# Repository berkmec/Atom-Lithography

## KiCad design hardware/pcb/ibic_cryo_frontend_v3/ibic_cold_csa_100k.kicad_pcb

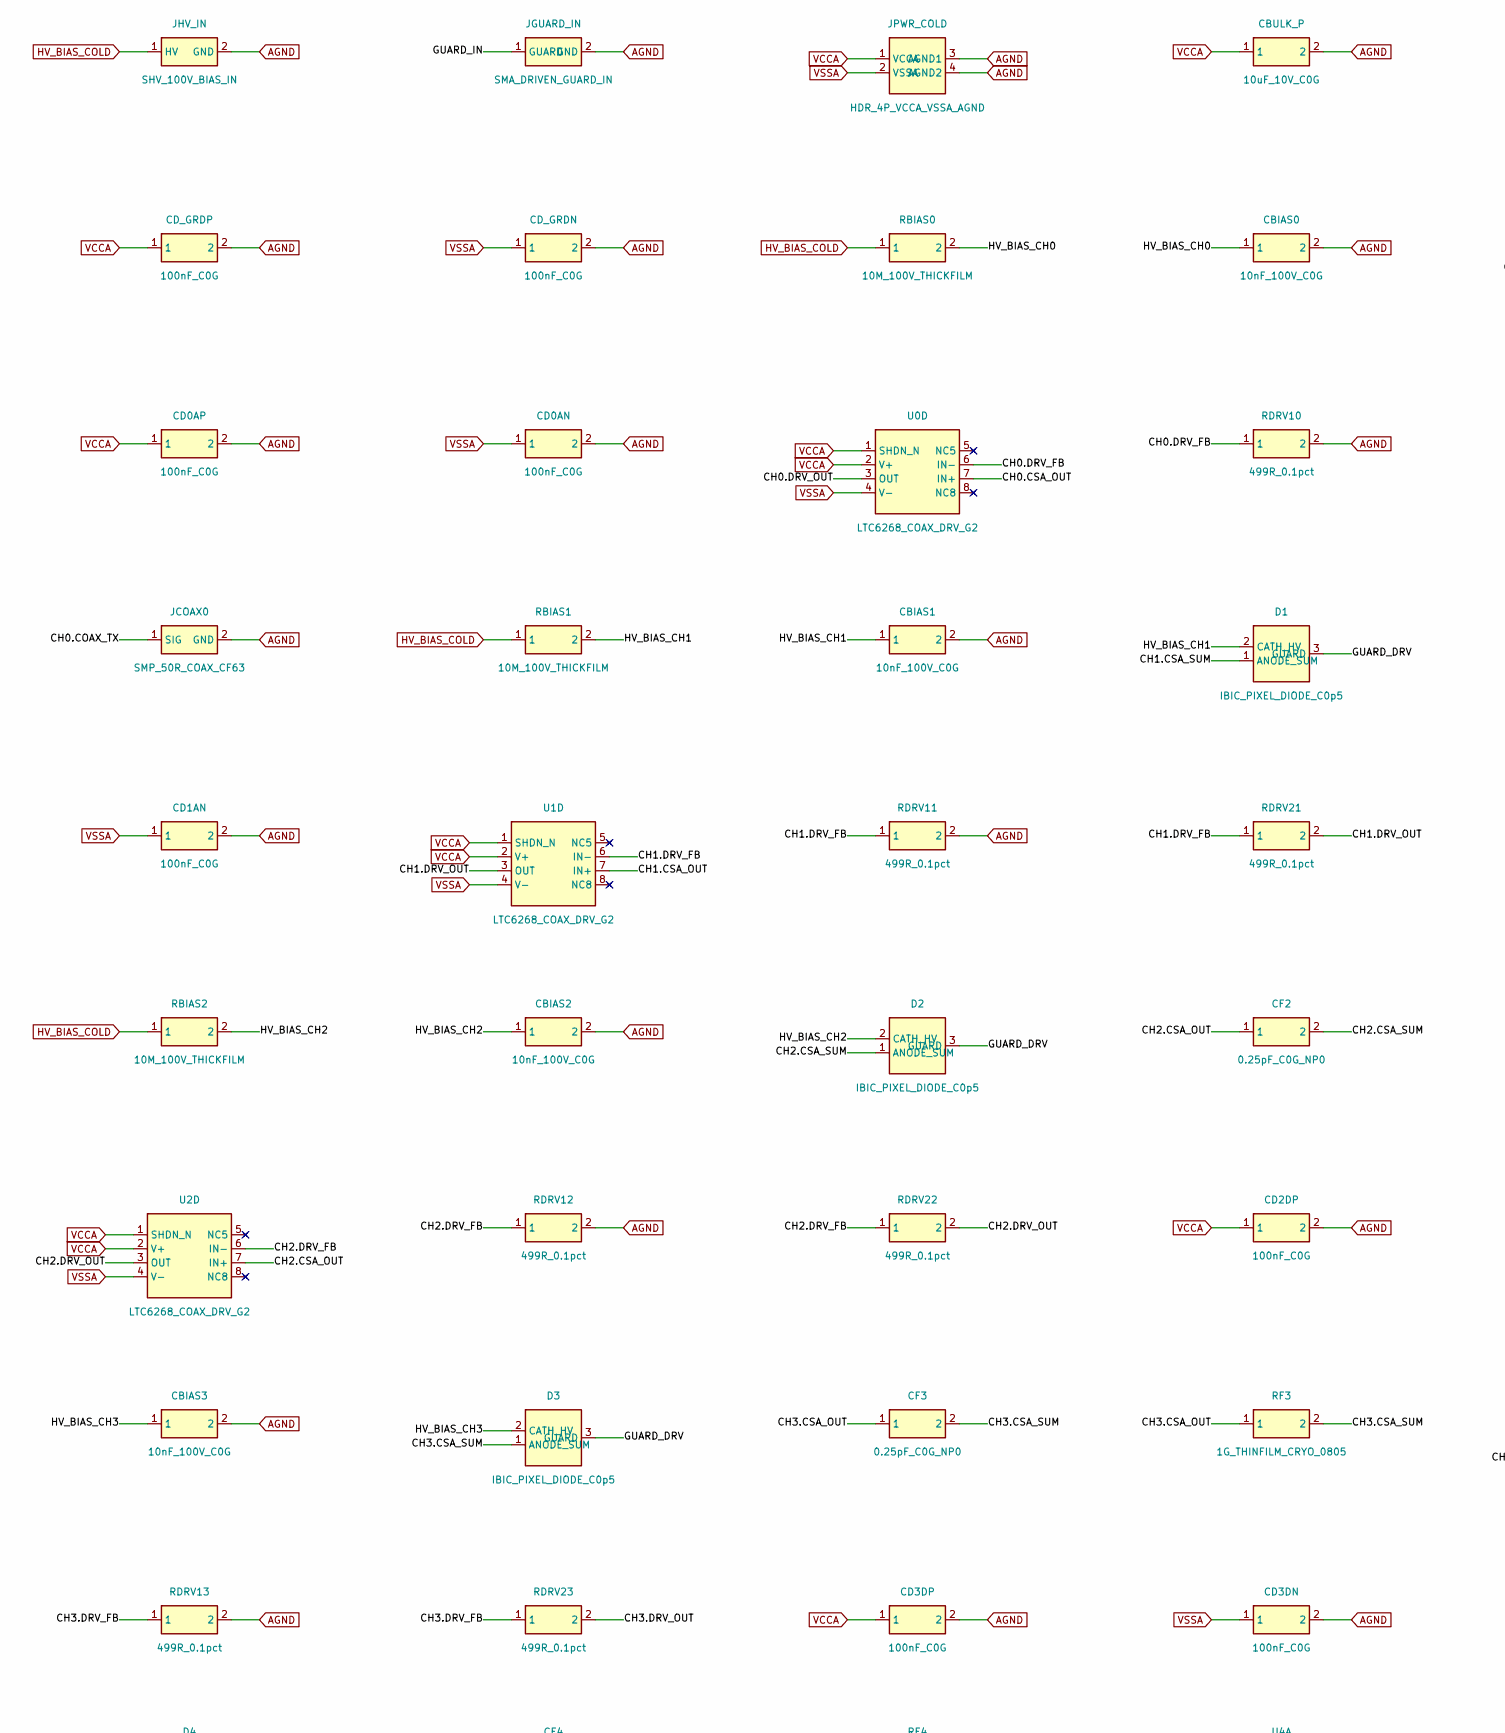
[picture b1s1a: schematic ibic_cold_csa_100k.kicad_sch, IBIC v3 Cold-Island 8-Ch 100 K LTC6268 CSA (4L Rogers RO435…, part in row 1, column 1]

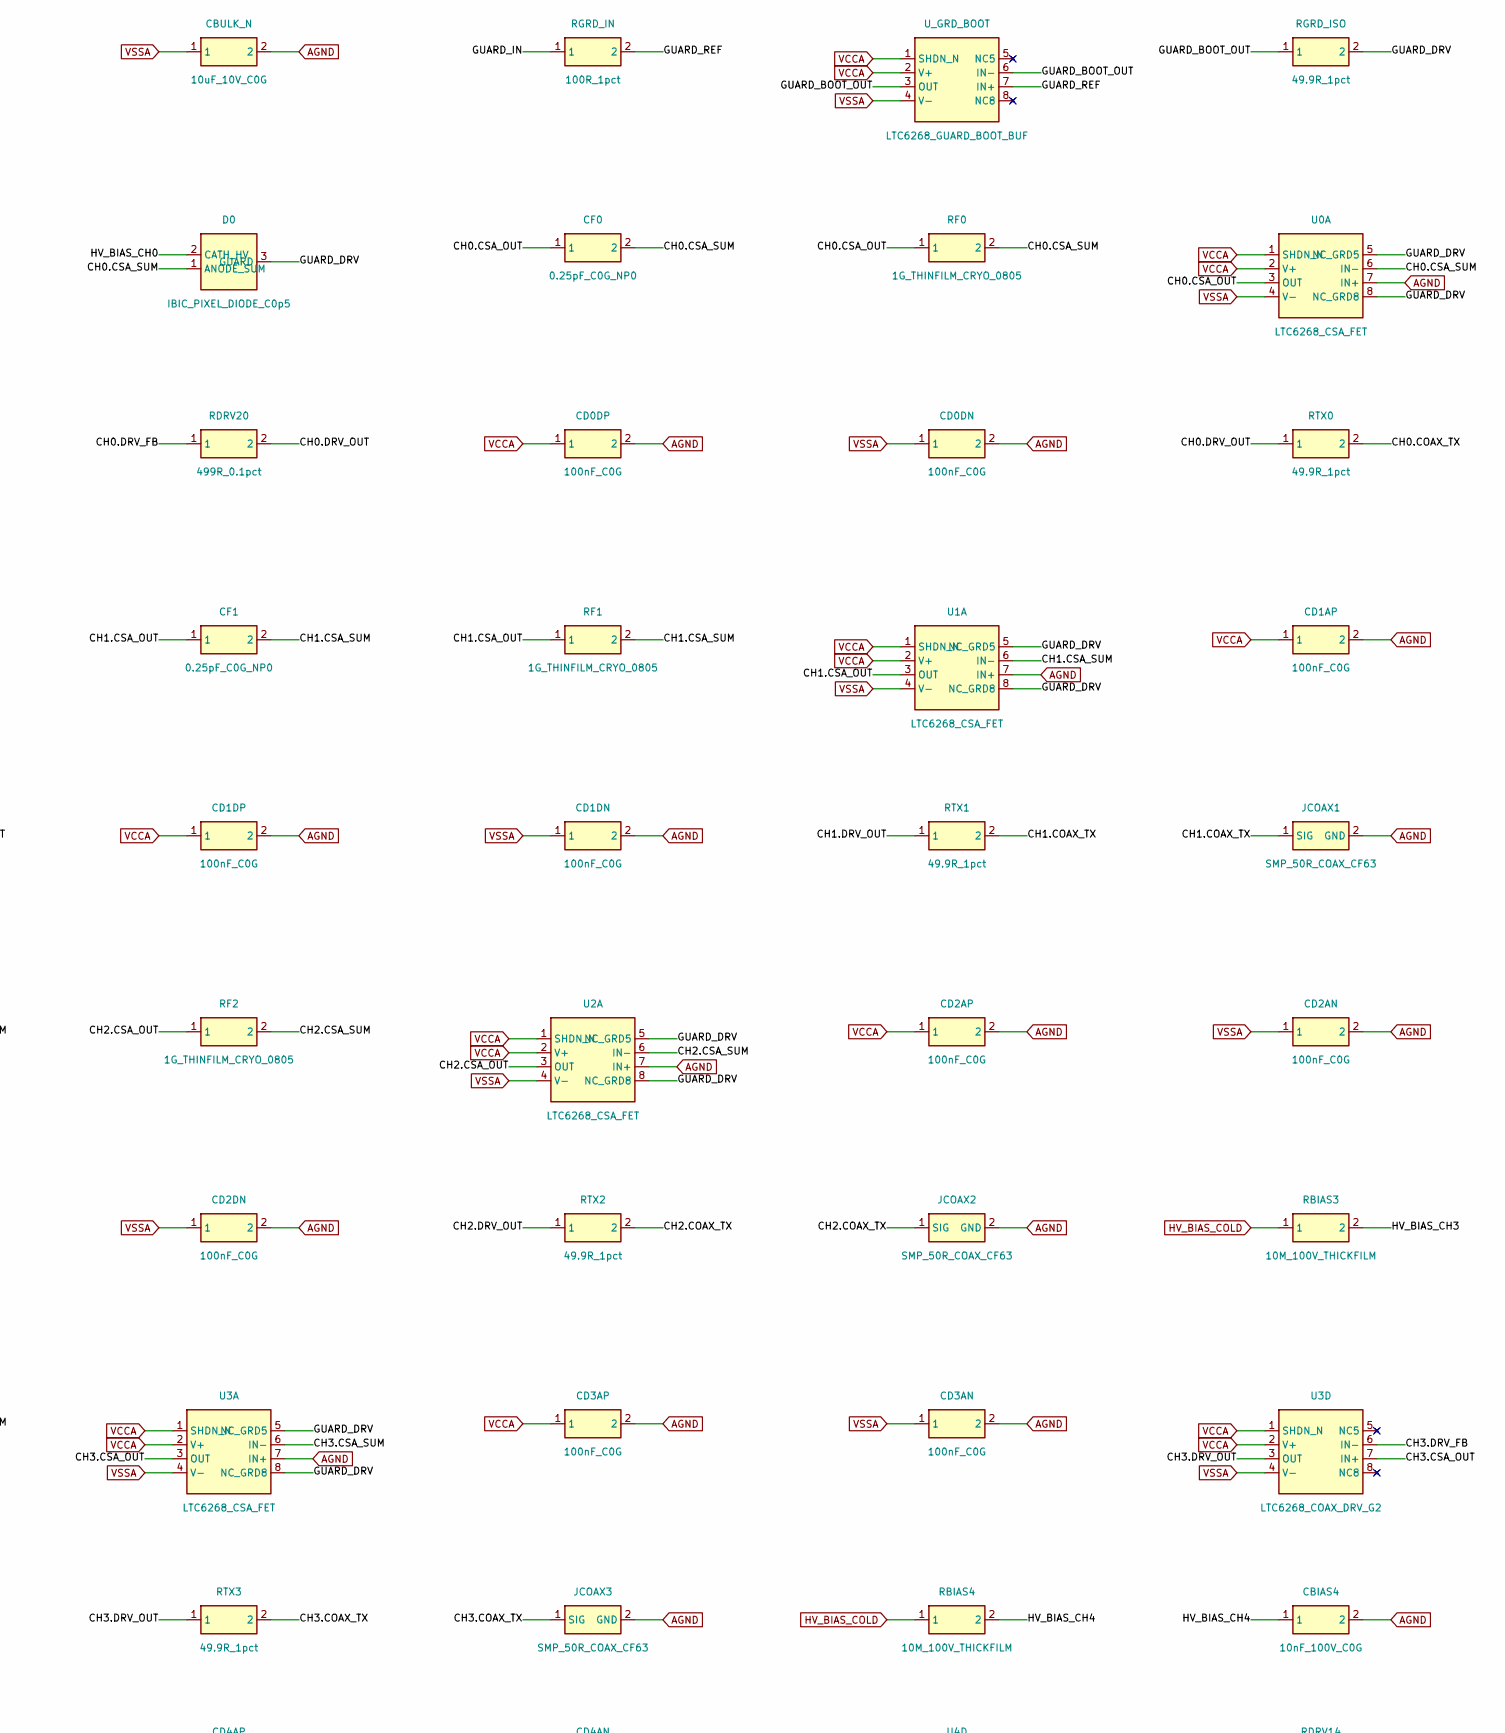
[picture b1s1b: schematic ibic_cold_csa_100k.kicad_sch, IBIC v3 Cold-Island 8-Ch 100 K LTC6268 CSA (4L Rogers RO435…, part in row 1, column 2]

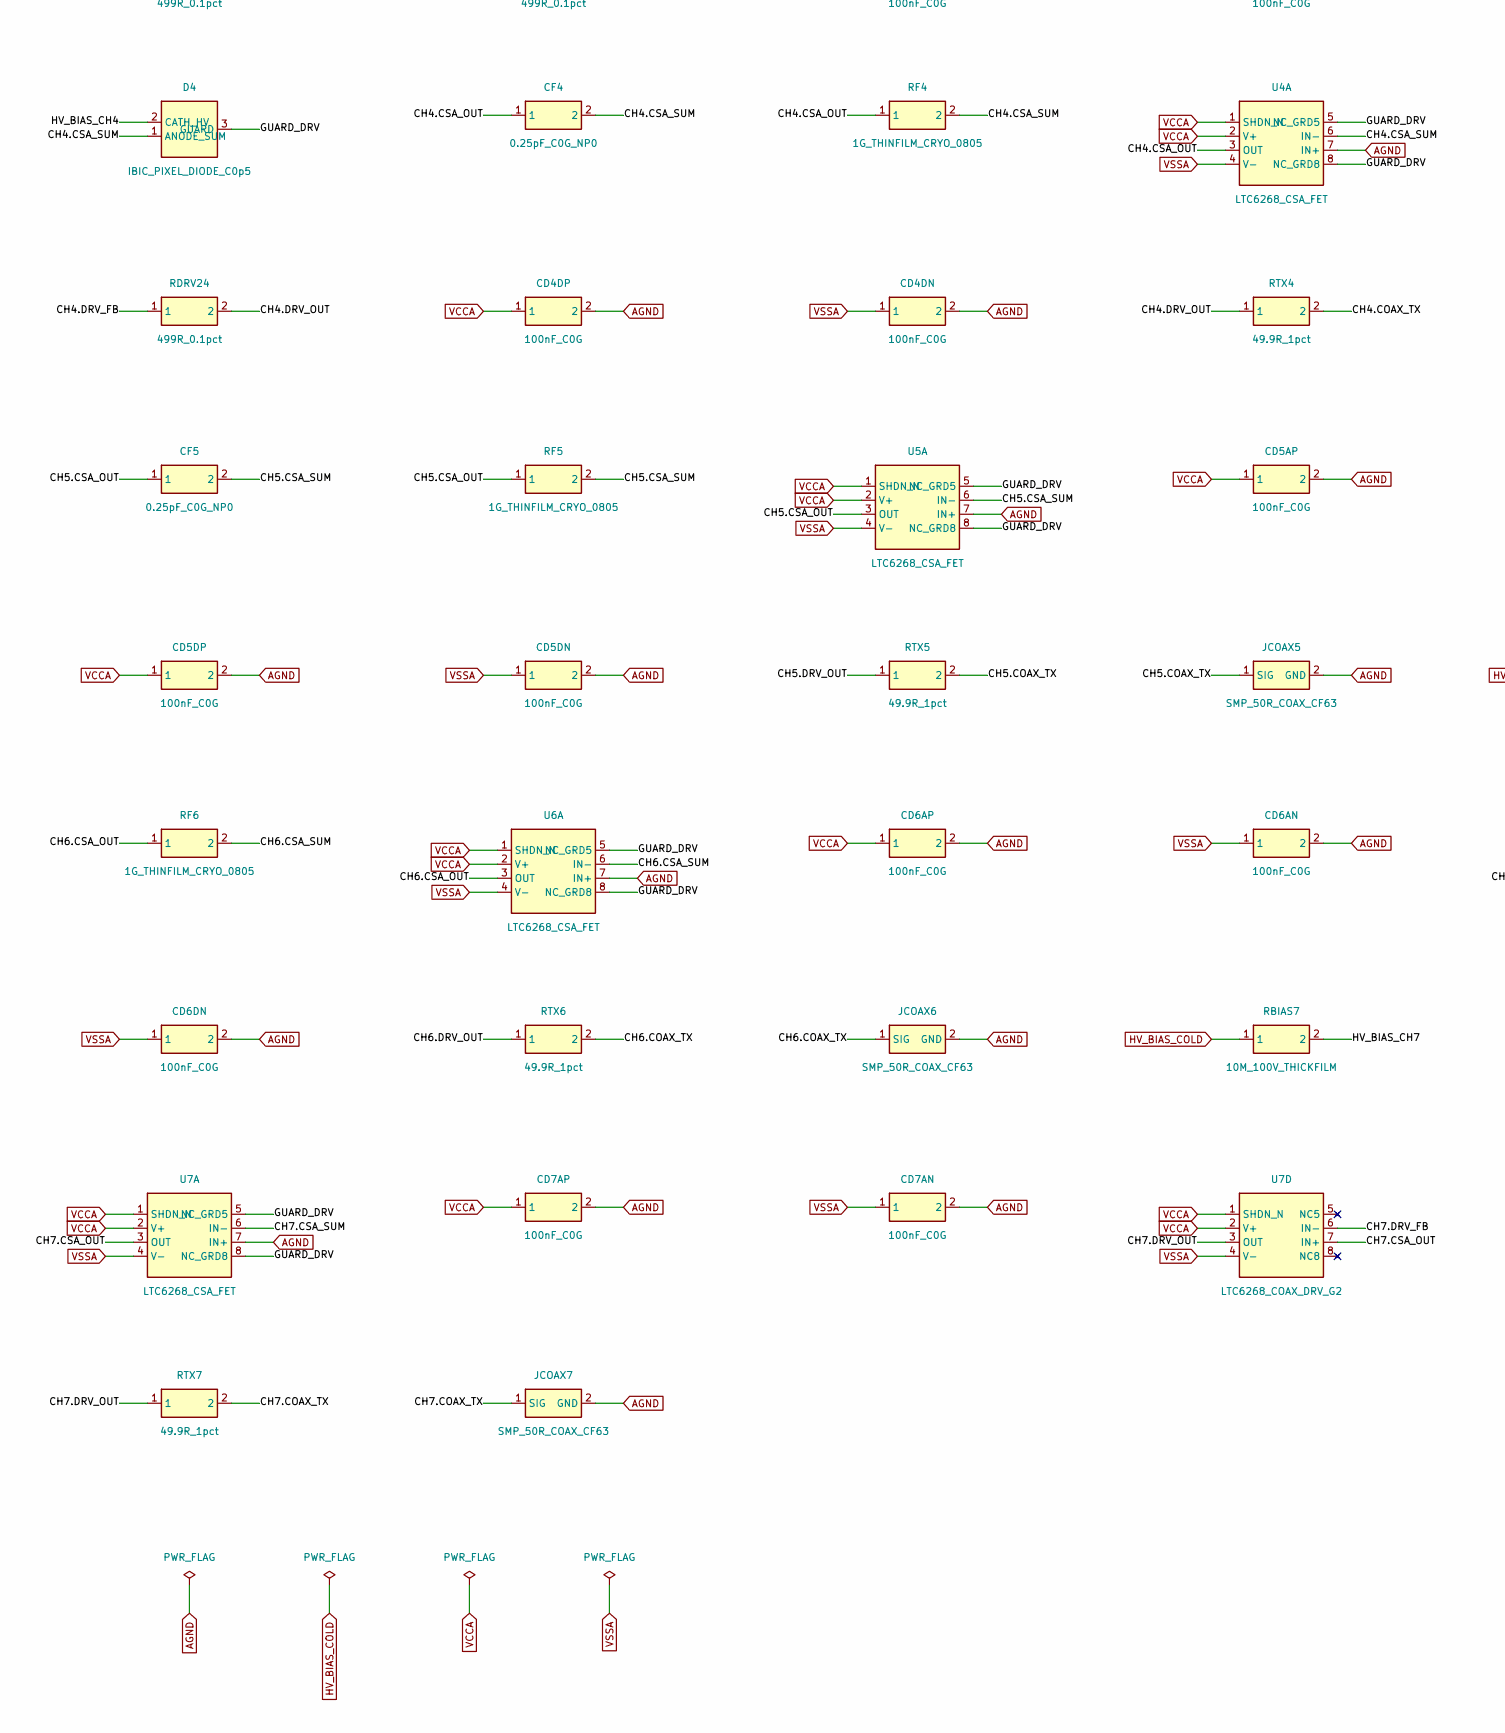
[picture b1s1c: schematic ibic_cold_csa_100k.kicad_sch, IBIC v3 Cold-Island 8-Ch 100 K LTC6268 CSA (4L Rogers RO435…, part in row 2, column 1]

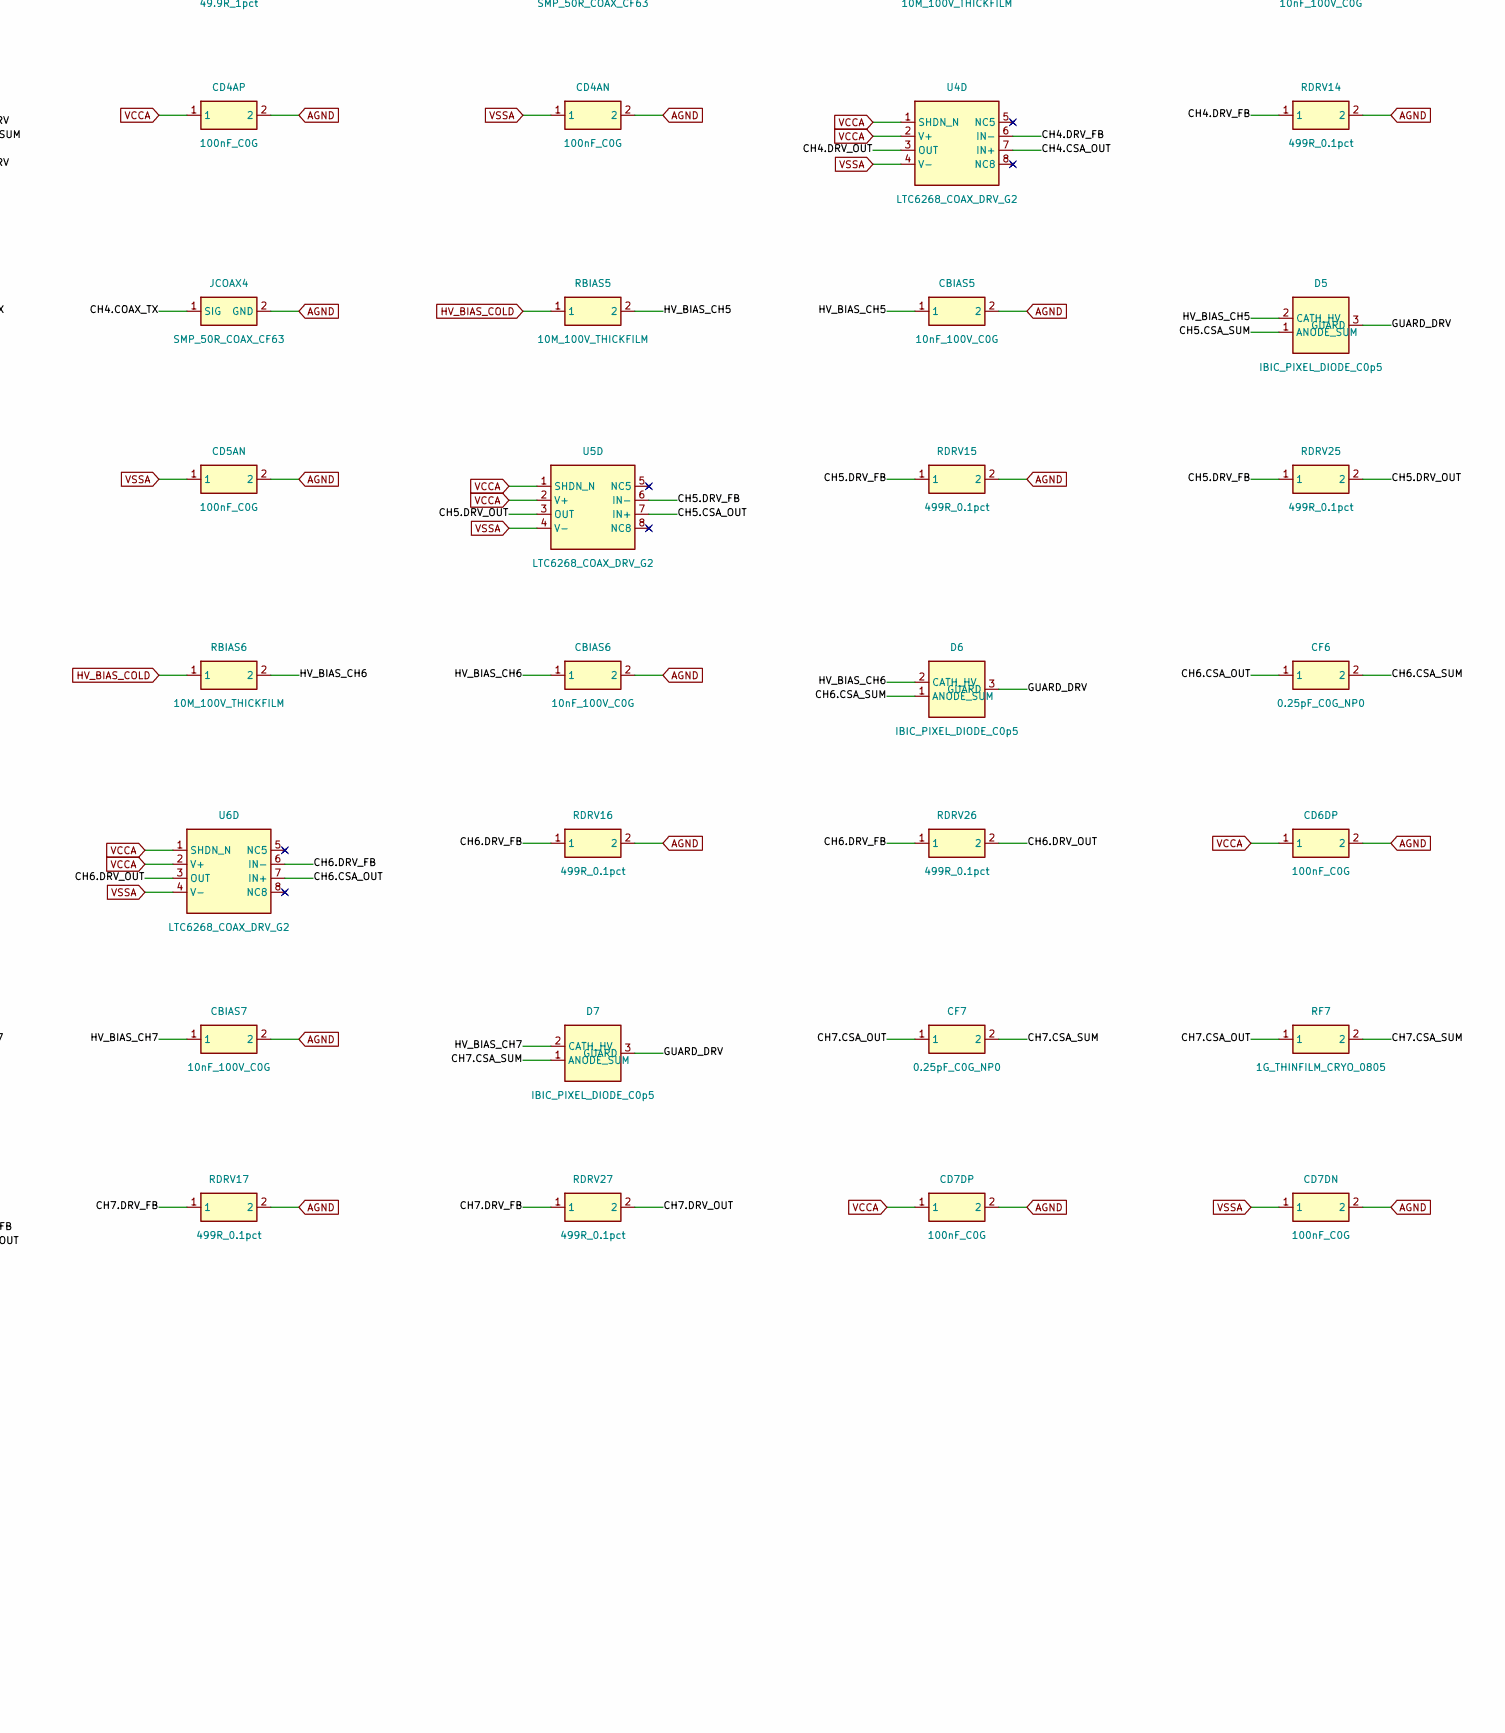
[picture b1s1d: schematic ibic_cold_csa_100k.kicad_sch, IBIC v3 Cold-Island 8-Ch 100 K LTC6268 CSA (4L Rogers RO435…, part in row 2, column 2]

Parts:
CBIAS0, CBIAS1, CBIAS2, CBIAS3, CBIAS4, CBIAS5, CBIAS6, CBIAS7: 10nF_100V_C0G; C_1206_3216Metric; MPN 10nF_100V_C0G
CBULK_N: 10uF_10V_C0G; C_0805_2012Metric; MPN 10uF_10V_C0G
CBULK_P: 10uF_10V_C0G; C_0805_2012Metric; MPN 10uF_10V_C0G
CD0AN, CD0AP, CD0DN, CD0DP, CD1AN, CD1AP, CD1DN, CD1DP, CD2AN, CD2AP, CD2DN, CD2DP, CD3AN, CD3AP, CD3DN, CD3DP, CD4AN, CD4AP, CD4DN, CD4DP, CD5AN, CD5AP, CD5DN, CD5DP, CD6AN, CD6AP, CD6DN, CD6DP, CD7AN, CD7AP, CD7DN, CD7DP: 100nF_C0G; C_0402_1005Metric; MPN 100nF_C0G
CD_GRDN: 100nF_C0G; C_0402_1005Metric; MPN 100nF_C0G
CD_GRDP: 100nF_C0G; C_0402_1005Metric; MPN 100nF_C0G
CF0, CF1, CF2, CF3, CF4, CF5, CF6, CF7: 0.25pF_C0G_NP0; C_0402_1005Metric; MPN 0.25pF_C0G_NP0
D0, D1, D2, D3, D4, D5, D6, D7: IBIC_PIXEL_DIODE_C0p5; IBIC_PIXEL_FLIPCHIP_3P; MPN IBIC_PIXEL_DIODE_C0p5
JCOAX0, JCOAX1, JCOAX2, JCOAX3, JCOAX4, JCOAX5, JCOAX6, JCOAX7: SMP_50R_COAX_CF63; SMA_EdgeMount; MPN SMP_50R_COAX_CF63
JGUARD_IN: SMA_DRIVEN_GUARD_IN; SMA_EdgeMount; MPN SMA_DRIVEN_GUARD_IN
JHV_IN: SHV_100V_BIAS_IN; SHV_Amphenol_HV; MPN SHV_100V_BIAS_IN
JPWR_COLD: HDR_4P_VCCA_VSSA_AGND; HDR_1x4_2.54mm; MPN HDR_4P_VCCA_VSSA_AGND
RBIAS0, RBIAS1, RBIAS2, RBIAS3, RBIAS4, RBIAS5, RBIAS6, RBIAS7: 10M_100V_THICKFILM; R_1206_3216Metric; MPN 10M_100V_THICKFILM
RDRV10, RDRV11, RDRV12, RDRV13, RDRV14, RDRV15, RDRV16, RDRV17, RDRV20, RDRV21, RDRV22, RDRV23, RDRV24, RDRV25, RDRV26, RDRV27: 499R_0.1pct; R_0402_1005Metric; MPN 499R_0.1pct
RF0, RF1, RF2, RF3, RF4, RF5, RF6, RF7: 1G_THINFILM_CRYO_0805; R_0805_2012Metric; MPN CHV0805-1G0-THINFILM-CRYO
RGRD_IN: 100R_1pct; R_0603_1608Metric; MPN 100R_1pct
RGRD_ISO: 49.9R_1pct; R_0603_1608Metric; MPN 49.9R_1pct
RTX0, RTX1, RTX2, RTX3, RTX4, RTX5, RTX6, RTX7: 49.9R_1pct; R_0402_1005Metric; MPN 49.9R_1pct
U0A, U1A, U2A, U3A, U4A, U5A, U6A, U7A: LTC6268_CSA_FET; SOIC-8_3.9x4.9mm_P1.27mm; MPN LTC6268IS8
U0D, U1D, U2D, U3D, U4D, U5D, U6D, U7D: LTC6268_COAX_DRV_G2; SOIC-8_3.9x4.9mm_P1.27mm; MPN LTC6268IS8
U_GRD_BOOT: LTC6268_GUARD_BOOT_BUF; SOIC-8_3.9x4.9mm_P1.27mm; MPN LTC6268IS8

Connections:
AGND: CBIAS0.2, CBIAS1.2, CBIAS2.2, CBIAS3.2, CBIAS4.2, CBIAS5.2, CBIAS6.2, CBIAS7.2, CBULK_N.2, CBULK_P.2, CD0AN.2, CD0AP.2, CD0DN.2, CD0DP.2, CD1AN.2, CD1AP.2, CD1DN.2, CD1DP.2, CD2AN.2, CD2AP.2, CD2DN.2, CD2DP.2, CD3AN.2, CD3AP.2, CD3DN.2, CD3DP.2, CD4AN.2, CD4AP.2, CD4DN.2, CD4DP.2, CD5AN.2, CD5AP.2, CD5DN.2, CD5DP.2, CD6AN.2, CD6AP.2, CD6DN.2, CD6DP.2, CD7AN.2, CD7AP.2, CD7DN.2, CD7DP.2, CD_GRDN.2, CD_GRDP.2, JCOAX0.2 (GND), JCOAX1.2 (GND), JCOAX2.2 (GND), JCOAX3.2 (GND), JCOAX4.2 (GND), JCOAX5.2 (GND), JCOAX6.2 (GND), JCOAX7.2 (GND), JGUARD_IN.2 (GND), JHV_IN.2 (GND), JPWR_COLD.3 (AGND1), JPWR_COLD.4 (AGND2), RDRV10.2, RDRV11.2, RDRV12.2, RDRV13.2, RDRV14.2, RDRV15.2, RDRV16.2, RDRV17.2, U0A.7 (IN+), U1A.7 (IN+), U2A.7 (IN+), U3A.7 (IN+), U4A.7 (IN+), U5A.7 (IN+), U6A.7 (IN+), U7A.7 (IN+)
CH0.COAX_TX: JCOAX0.1 (SIG), RTX0.2
CH0.CSA_OUT: CF0.1, RF0.1, U0A.3 (OUT), U0D.7 (IN+)
CH0.CSA_SUM: CF0.2, D0.1 (ANODE_SUM), RF0.2, U0A.6 (IN-)
CH0.DRV_FB: RDRV10.1, RDRV20.1, U0D.6 (IN-)
CH0.DRV_OUT: RDRV20.2, RTX0.1, U0D.3 (OUT)
CH1.COAX_TX: JCOAX1.1 (SIG), RTX1.2
CH1.CSA_OUT: CF1.1, RF1.1, U1A.3 (OUT), U1D.7 (IN+)
CH1.CSA_SUM: CF1.2, D1.1 (ANODE_SUM), RF1.2, U1A.6 (IN-)
CH1.DRV_FB: RDRV11.1, RDRV21.1, U1D.6 (IN-)
CH1.DRV_OUT: RDRV21.2, RTX1.1, U1D.3 (OUT)
CH2.COAX_TX: JCOAX2.1 (SIG), RTX2.2
CH2.CSA_OUT: CF2.1, RF2.1, U2A.3 (OUT), U2D.7 (IN+)
CH2.CSA_SUM: CF2.2, D2.1 (ANODE_SUM), RF2.2, U2A.6 (IN-)
CH2.DRV_FB: RDRV12.1, RDRV22.1, U2D.6 (IN-)
CH2.DRV_OUT: RDRV22.2, RTX2.1, U2D.3 (OUT)
CH3.COAX_TX: JCOAX3.1 (SIG), RTX3.2
CH3.CSA_OUT: CF3.1, RF3.1, U3A.3 (OUT), U3D.7 (IN+)
CH3.CSA_SUM: CF3.2, D3.1 (ANODE_SUM), RF3.2, U3A.6 (IN-)
CH3.DRV_FB: RDRV13.1, RDRV23.1, U3D.6 (IN-)
CH3.DRV_OUT: RDRV23.2, RTX3.1, U3D.3 (OUT)
CH4.COAX_TX: JCOAX4.1 (SIG), RTX4.2
CH4.CSA_OUT: CF4.1, RF4.1, U4A.3 (OUT), U4D.7 (IN+)
CH4.CSA_SUM: CF4.2, D4.1 (ANODE_SUM), RF4.2, U4A.6 (IN-)
CH4.DRV_FB: RDRV14.1, RDRV24.1, U4D.6 (IN-)
CH4.DRV_OUT: RDRV24.2, RTX4.1, U4D.3 (OUT)
CH5.COAX_TX: JCOAX5.1 (SIG), RTX5.2
CH5.CSA_OUT: CF5.1, RF5.1, U5A.3 (OUT), U5D.7 (IN+)
CH5.CSA_SUM: CF5.2, D5.1 (ANODE_SUM), RF5.2, U5A.6 (IN-)
CH5.DRV_FB: RDRV15.1, RDRV25.1, U5D.6 (IN-)
CH5.DRV_OUT: RDRV25.2, RTX5.1, U5D.3 (OUT)
CH6.COAX_TX: JCOAX6.1 (SIG), RTX6.2
CH6.CSA_OUT: CF6.1, RF6.1, U6A.3 (OUT), U6D.7 (IN+)
CH6.CSA_SUM: CF6.2, D6.1 (ANODE_SUM), RF6.2, U6A.6 (IN-)
CH6.DRV_FB: RDRV16.1, RDRV26.1, U6D.6 (IN-)
CH6.DRV_OUT: RDRV26.2, RTX6.1, U6D.3 (OUT)
CH7.COAX_TX: JCOAX7.1 (SIG), RTX7.2
CH7.CSA_OUT: CF7.1, RF7.1, U7A.3 (OUT), U7D.7 (IN+)
CH7.CSA_SUM: CF7.2, D7.1 (ANODE_SUM), RF7.2, U7A.6 (IN-)
CH7.DRV_FB: RDRV17.1, RDRV27.1, U7D.6 (IN-)
CH7.DRV_OUT: RDRV27.2, RTX7.1, U7D.3 (OUT)
GUARD_BOOT_OUT: RGRD_ISO.1, U_GRD_BOOT.3 (OUT), U_GRD_BOOT.6 (IN-)
GUARD_DRV: D0.3 (GUARD), D1.3 (GUARD), D2.3 (GUARD), D3.3 (GUARD), D4.3 (GUARD), D5.3 (GUARD), D6.3 (GUARD), D7.3 (GUARD), RGRD_ISO.2, U0A.5 (NC_GRD5), U0A.8 (NC_GRD8), U1A.5 (NC_GRD5), U1A.8 (NC_GRD8), U2A.5 (NC_GRD5), U2A.8 (NC_GRD8), U3A.5 (NC_GRD5), U3A.8 (NC_GRD8), U4A.5 (NC_GRD5), U4A.8 (NC_GRD8), U5A.5 (NC_GRD5), U5A.8 (NC_GRD8), U6A.5 (NC_GRD5), U6A.8 (NC_GRD8), U7A.5 (NC_GRD5), U7A.8 (NC_GRD8)
GUARD_IN: JGUARD_IN.1 (GUARD), RGRD_IN.1
GUARD_REF: RGRD_IN.2, U_GRD_BOOT.7 (IN+)
HV_BIAS_CH0: CBIAS0.1, D0.2 (CATH_HV), RBIAS0.2
HV_BIAS_CH1: CBIAS1.1, D1.2 (CATH_HV), RBIAS1.2
HV_BIAS_CH2: CBIAS2.1, D2.2 (CATH_HV), RBIAS2.2
HV_BIAS_CH3: CBIAS3.1, D3.2 (CATH_HV), RBIAS3.2
HV_BIAS_CH4: CBIAS4.1, D4.2 (CATH_HV), RBIAS4.2
HV_BIAS_CH5: CBIAS5.1, D5.2 (CATH_HV), RBIAS5.2
HV_BIAS_CH6: CBIAS6.1, D6.2 (CATH_HV), RBIAS6.2
HV_BIAS_CH7: CBIAS7.1, D7.2 (CATH_HV), RBIAS7.2
HV_BIAS_COLD: JHV_IN.1 (HV), RBIAS0.1, RBIAS1.1, RBIAS2.1, RBIAS3.1, RBIAS4.1, RBIAS5.1, RBIAS6.1, RBIAS7.1
VCCA: CBULK_P.1, CD0AP.1, CD0DP.1, CD1AP.1, CD1DP.1, CD2AP.1, CD2DP.1, CD3AP.1, CD3DP.1, CD4AP.1, CD4DP.1, CD5AP.1, CD5DP.1, CD6AP.1, CD6DP.1, CD7AP.1, CD7DP.1, CD_GRDP.1, JPWR_COLD.1 (VCCA), U0A.1 (SHDN_N), U0A.2 (V+), U0D.1 (SHDN_N), U0D.2 (V+), U1A.1 (SHDN_N), U1A.2 (V+), U1D.1 (SHDN_N), U1D.2 (V+), U2A.1 (SHDN_N), U2A.2 (V+), U2D.1 (SHDN_N), U2D.2 (V+), U3A.1 (SHDN_N), U3A.2 (V+), U3D.1 (SHDN_N), U3D.2 (V+), U4A.1 (SHDN_N), U4A.2 (V+), U4D.1 (SHDN_N), U4D.2 (V+), U5A.1 (SHDN_N), U5A.2 (V+), U5D.1 (SHDN_N), U5D.2 (V+), U6A.1 (SHDN_N), U6A.2 (V+), U6D.1 (SHDN_N), U6D.2 (V+), U7A.1 (SHDN_N), U7A.2 (V+), U7D.1 (SHDN_N), U7D.2 (V+), U_GRD_BOOT.1 (SHDN_N), U_GRD_BOOT.2 (V+)
VSSA: CBULK_N.1, CD0AN.1, CD0DN.1, CD1AN.1, CD1DN.1, CD2AN.1, CD2DN.1, CD3AN.1, CD3DN.1, CD4AN.1, CD4DN.1, CD5AN.1, CD5DN.1, CD6AN.1, CD6DN.1, CD7AN.1, CD7DN.1, CD_GRDN.1, JPWR_COLD.2 (VSSA), U0A.4 (V-), U0D.4 (V-), U1A.4 (V-), U1D.4 (V-), U2A.4 (V-), U2D.4 (V-), U3A.4 (V-), U3D.4 (V-), U4A.4 (V-), U4D.4 (V-), U5A.4 (V-), U5D.4 (V-), U6A.4 (V-), U6D.4 (V-), U7A.4 (V-), U7D.4 (V-), U_GRD_BOOT.4 (V-)

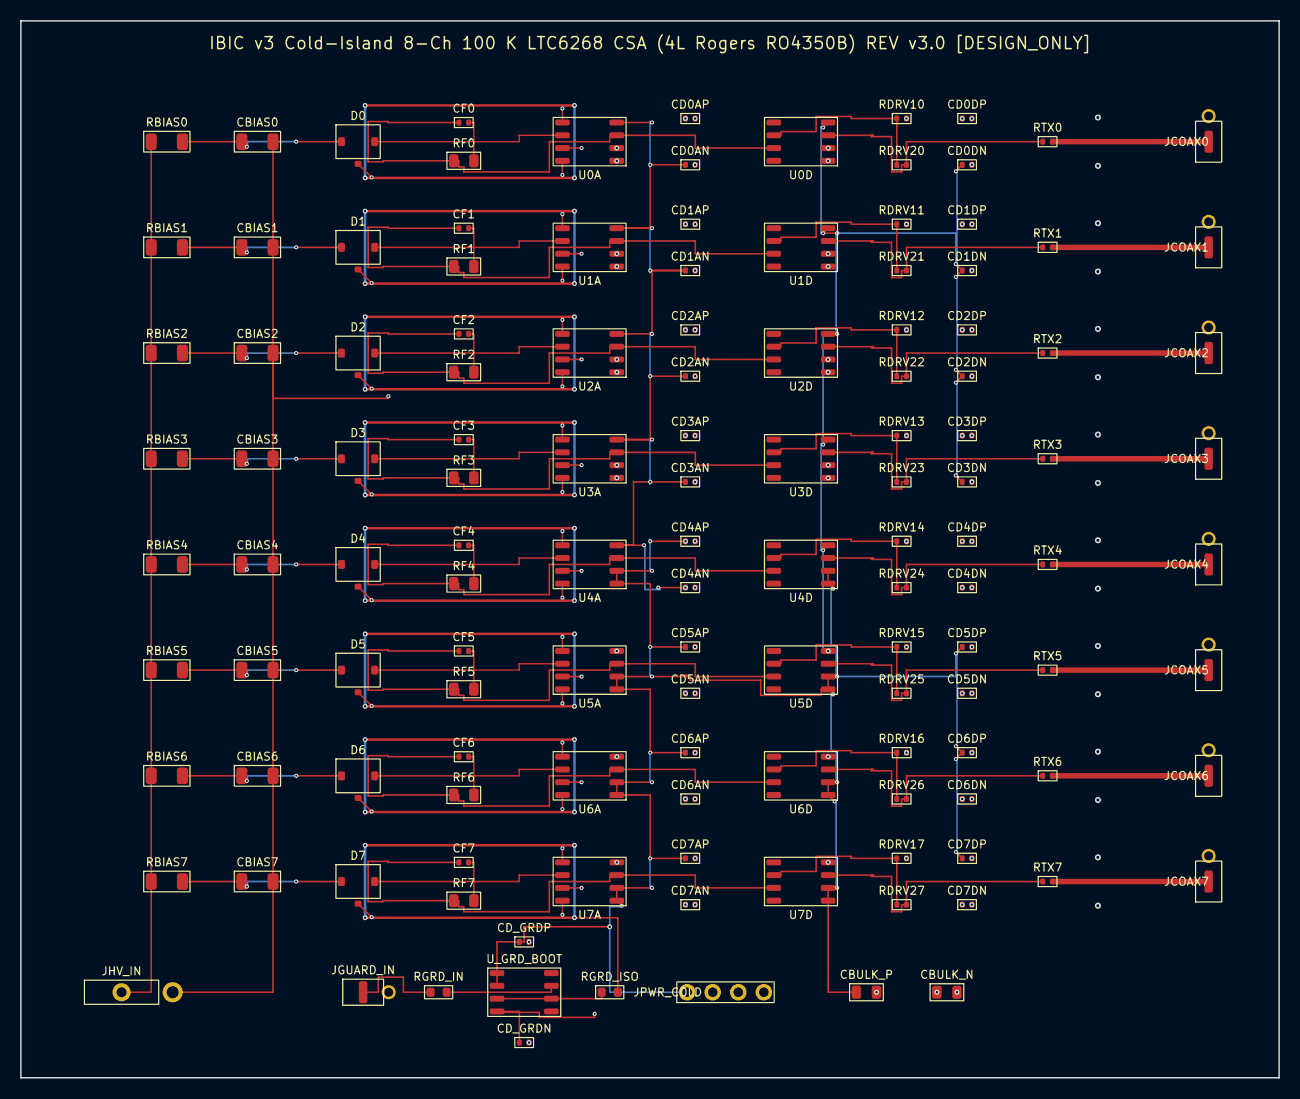
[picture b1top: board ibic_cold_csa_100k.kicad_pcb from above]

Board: 4 copper layers, 125.0 x 105.0 mm, 130 parts (0 on the bottom side), 56 nets.
